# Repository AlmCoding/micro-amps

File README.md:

# 🔬 µAmps – Open-Hardware Current-to-Voltage Converter

**µAmps** is an open-hardware current-to-voltage converter designed as a practical, low-cost alternative to the µCurrent GOLD. It allows precise conversion of extremely small currents into a measurable voltage across three optimized ranges, making it ideal for low-power electronics and embedded device development.

With its analog voltage output, µAmps can be easily connected to a multimeter, oscilloscope, or data acquisition system, enabling engineers and makers to debug and verify power consumption down to the nanoamp level.

[Buy on Tindie](INSERT_TINDIE_LINK_HERE)

## 🧾 Technical Specifications

- **Current Ranges:**
  - ±120 mA @ 1 Ω shunt ➜ 1 mV/10 µA  
  - ±1.2 mA @ 100 Ω shunt ➜ 1 mV/0.1 µA  
  - ±12 µA @ 10 kΩ shunt ➜ 1 mV/nA
- **Output Voltage Range:** ±12 V
- **Output Offset Voltage:** <10 µV (@25°C)
- **Bandwidth:** >70 kHz (-3 dB)
- **Accuracy (typical):**
  - ±0.05% on µA and nA ranges  
  - ±1% on mA range
- **Battery:** 2x A23 (±12V)

## 🎯 Perfect For

- Measuring sleep currents of microcontrollers and low-power devices  
- Validating energy-saving or standby modes  
- Debugging ultra-low power electronics  
- Educational and experimental applications

The analog output allows direct measurement with standard lab equipment, providing a simple and effective way to monitor tiny currents in real-time.

## 🛠️ Open Hardware Files

All design files are open and available for use under the **CERN OHL v2** license:

- PCB design files (KiCad 9.0)  
- Schematic diagrams  
- Bill of Materials (BOM)  

Contributions, improvements, and forks are welcome. Please respect the original licensing terms.

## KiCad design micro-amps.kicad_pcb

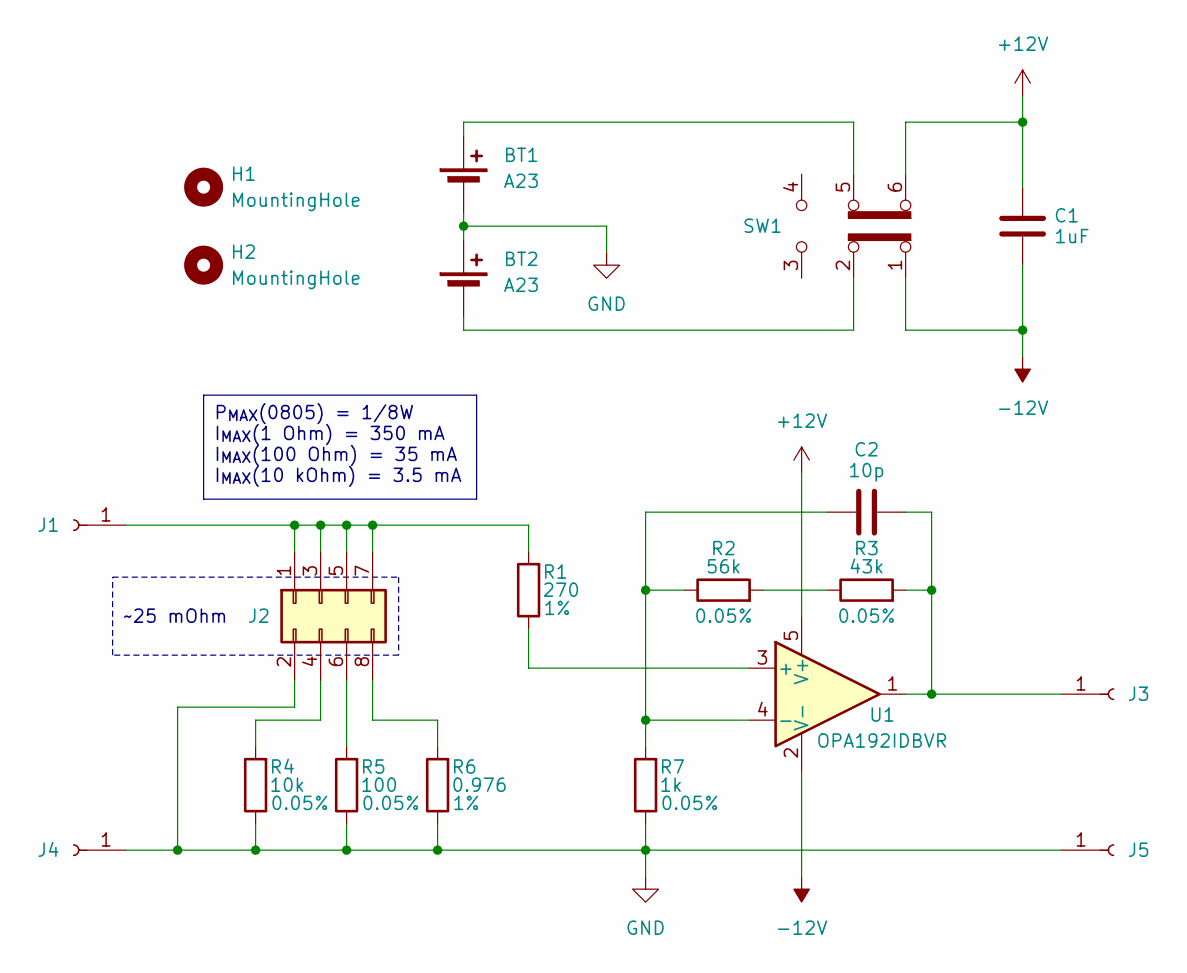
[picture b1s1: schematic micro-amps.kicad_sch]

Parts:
BT1, BT2: A23; A23_Battery_Holder_Keystone_82
C1: 1uF; C_0805_2012Metric_Pad1.18x1.45mm_HandSolder
C2: 10p; C_0603_1608Metric_Pad1.08x0.95mm_HandSolder
H1, H2: MountingHole; MountingHole_3.2mm_M3
J1, J3, J4, J5: Conn_01x01_Socket; Banana_Jack_1Pin
J2: Conn_02x04_Odd_Even; PinHeader_2x04_P2.54mm_Vertical
R1: 270; R_0603_1608Metric_Pad0.98x0.95mm_HandSolder; Tolerance 1%
R2: 56k; R_0603_1608Metric_Pad0.98x0.95mm_HandSolder; Tolerance 0.05%
R3: 43k; R_0603_1608Metric_Pad0.98x0.95mm_HandSolder; Tolerance 0.05%
R4: 10k; R_0805_2012Metric_Pad1.20x1.40mm_HandSolder; Tolerance 0.05%
R5: 100; R_0805_2012Metric_Pad1.20x1.40mm_HandSolder; Tolerance 0.05%
R6: 0.976; R_0805_2012Metric_Pad1.20x1.40mm_HandSolder; Tolerance 1%
R7: 1k; R_0603_1608Metric_Pad0.98x0.95mm_HandSolder; Tolerance 0.05%
SW1: SW_Slide_DPDT; SW_DPDT_SLW_913535
U1: OPA192IDBVR; SOT-23-5_HandSoldering

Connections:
+12V: C1.1, SW1.6 (C), U1.5 (V+)
-12V: C1.2, SW1.1 (A), U1.2 (V-)
GND: BT1.2 (-), BT2.1 (+), J2.2, J4.1, J5.1, R4.1, R5.1, R6.1, R7.1
unnamed: BT1.1 (+), SW1.5 (B)
unnamed: BT2.2 (-), SW1.2 (B)
unnamed: J1.1, J2.1, J2.3, J2.5, J2.7, R1.2
unnamed: J2.4, R4.2
unnamed: J2.6, R5.2
unnamed: J2.8, R6.2
unnamed: C2.1, J3.1, R3.2, U1.1
unnamed: R2.2, R3.1
unnamed: R1.1, U1.3 (+)
unnamed: C2.2, R2.1, R7.2, U1.4 (-)

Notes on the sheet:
~25 mOhm
P_{MAX}(0805) = 1/8W I_{MAX}(1 Ohm) = 350 mA I_{MAX}(100 Ohm) = 35 mA I_{MAX}(10 kOhm) = 3.5 mA

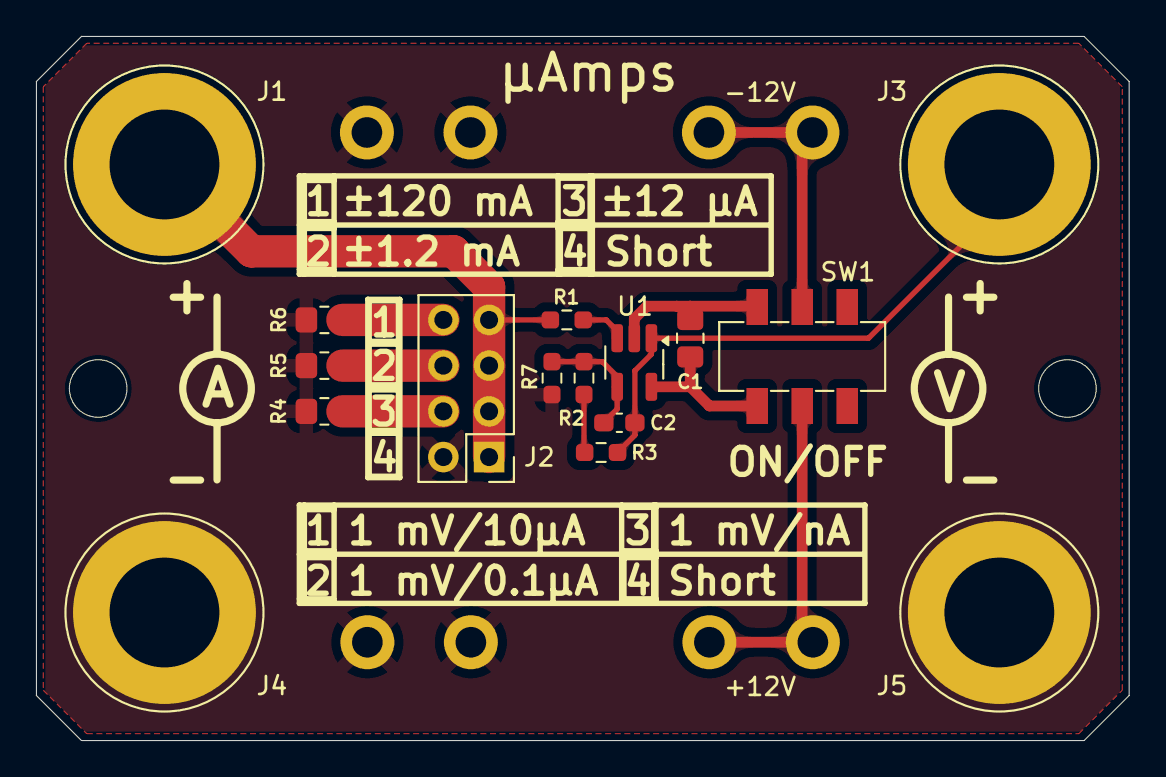
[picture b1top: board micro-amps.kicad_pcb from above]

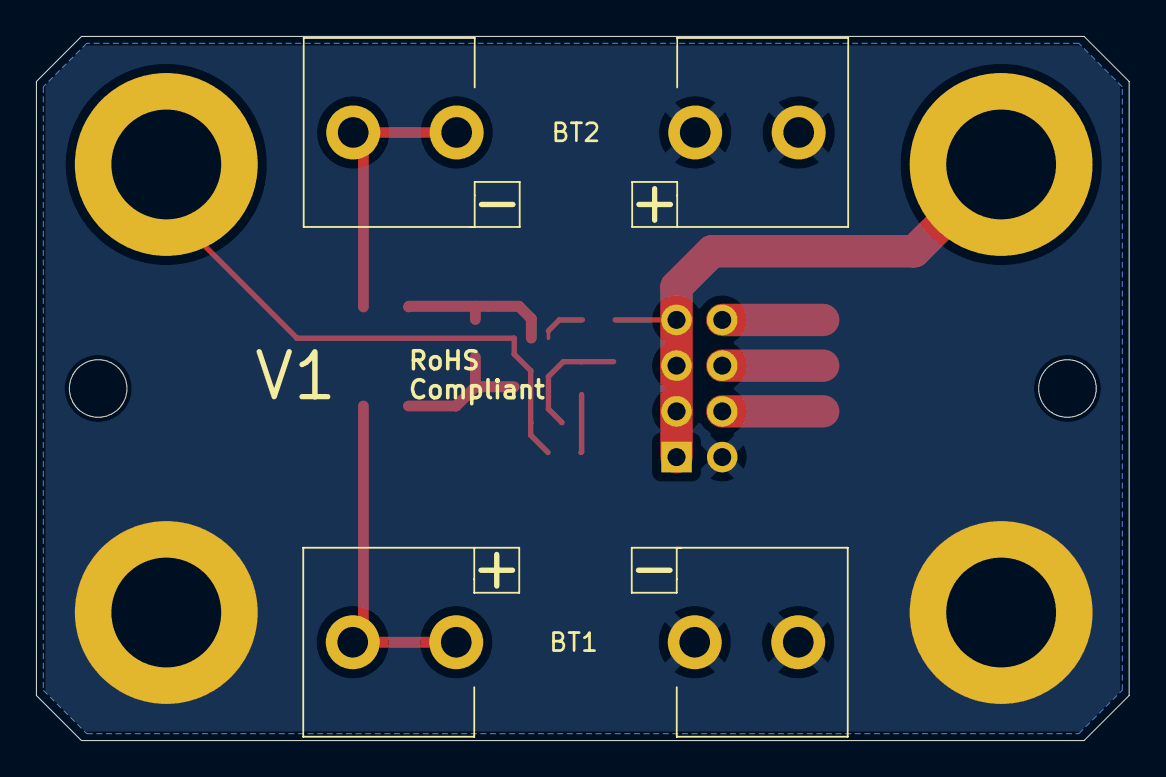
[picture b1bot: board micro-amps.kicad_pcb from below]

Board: 2 copper layers, 60.7 x 39.1 mm, 20 parts (2 on the bottom side), 13 nets.

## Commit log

2025-11-01 Single OPAMP stage
2025-11-02 Dual OPAMP stage
2025-11-02 Optimize layout
2025-11-10 Refine things
2025-11-10 Update readme + add license
